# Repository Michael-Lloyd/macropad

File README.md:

# Bluetooth Macropad

Wireless macropad/keypad with programmable keys that lasts a long time between charges. Has some interesting features.

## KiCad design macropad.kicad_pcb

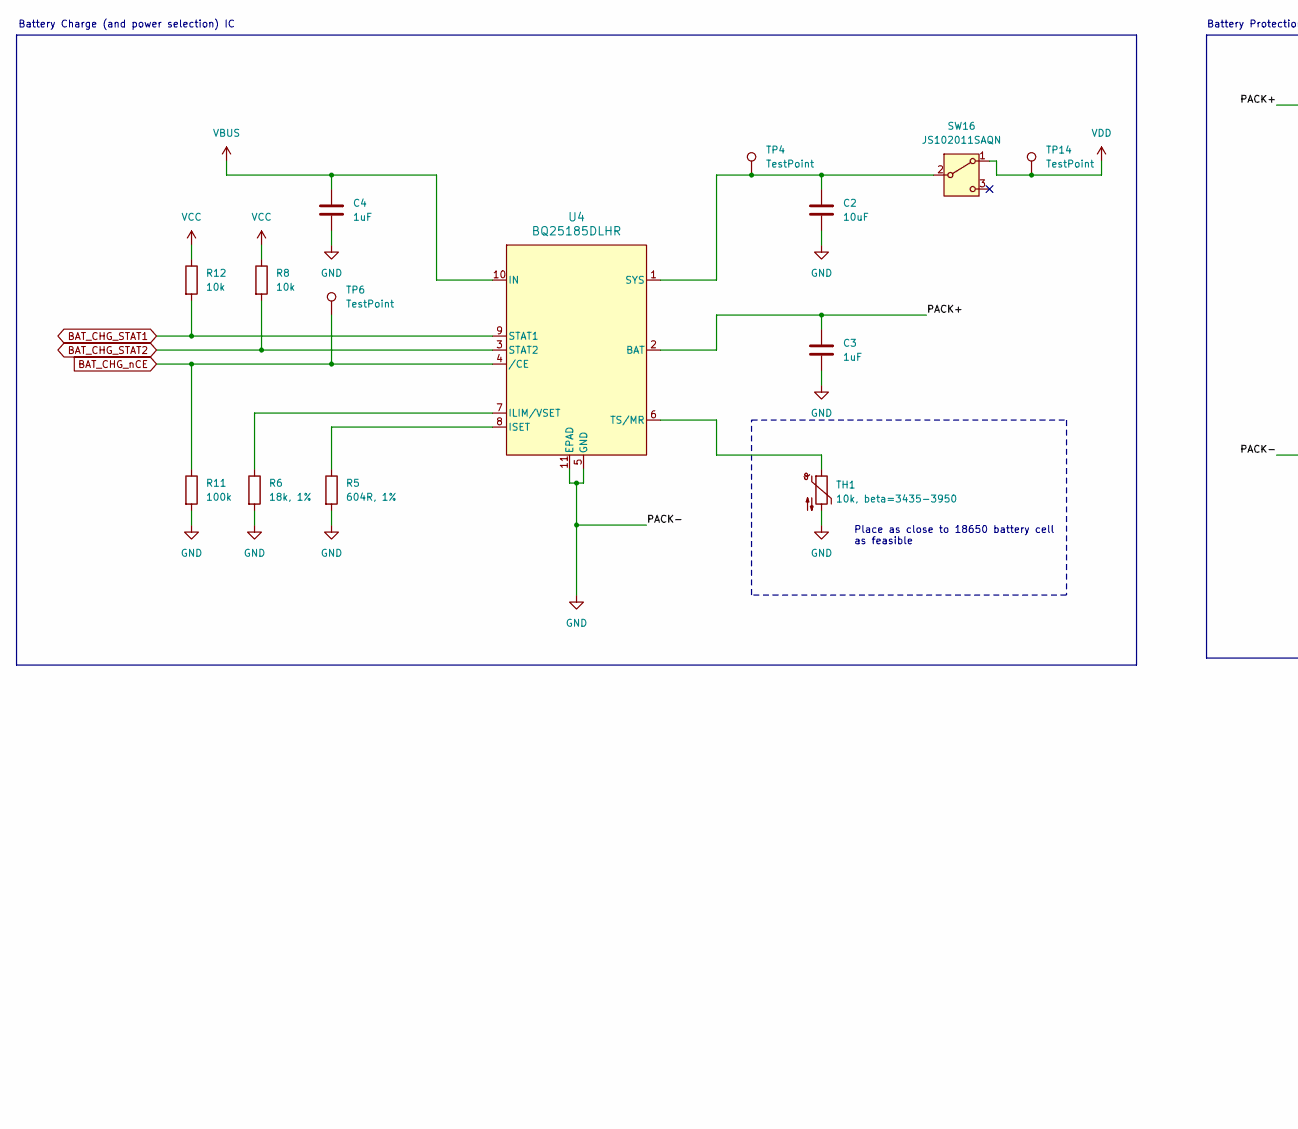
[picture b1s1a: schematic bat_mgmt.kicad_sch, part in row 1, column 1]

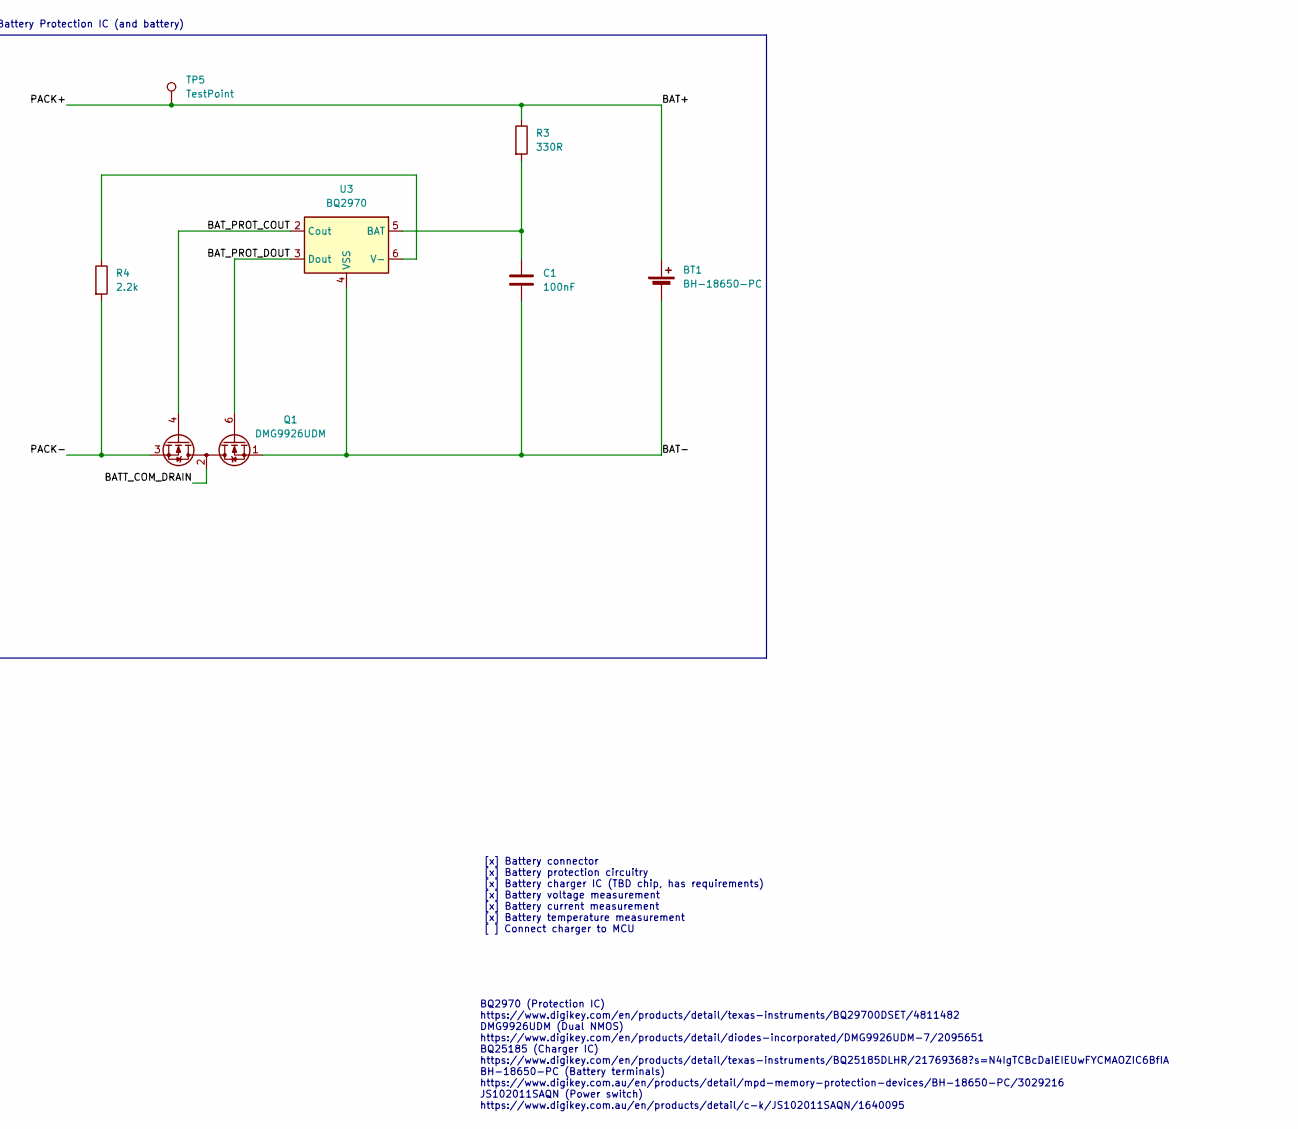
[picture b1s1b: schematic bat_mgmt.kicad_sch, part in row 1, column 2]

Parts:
BT1: BH-18650-PC; BH18650PC
C1: 100nF; C_0402_1005Metric
C2: 10uF; C_0603_1608Metric
C3, C4: 1uF; C_0603_1608Metric
Q1: DMG9926UDM; SOT-23-6
R3: 330R; R_0402_1005Metric
R4: 2.2k; R_0402_1005Metric
R5: 604R, 1%; R_0402_1005Metric
R6: 18k, 1%; R_0402_1005Metric
R8, R12: 10k; R_0402_1005Metric
R11: 100k; R_0402_1005Metric
SW16: JS102011SAQN; SW_SPDT_CK_JS102011SAQN
TH1: 10k, beta=3435-3950; R_0603_1608Metric
TP4, TP5, TP6, TP14: TestPoint; TestPoint_Pad_D0.5mm
U3: BQ2970; WSON-6_1.5x1.5mm_P0.5mm
U4: BQ25185DLHR

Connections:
/Power and Battery Management/BAT+: BT1.1 (+), C3.1, R3.1, TP5.1, U4.2 (BAT)
/Power and Battery Management/BAT-: BT1.2 (-), C1.2, Q1.1 (S1), U3.4 (VSS)
/Power and Battery Management/BATT_COM_DRAIN: Q1.2 (D1/D2), Q1.5 (D1/D2)
/Power and Battery Management/BAT_PROT_COUT: Q1.4 (G2), U3.2 (Cout)
/Power and Battery Management/BAT_PROT_DOUT: Q1.6 (G1), U3.3 (Dout)
BAT_CHG_STAT1: R12.2, U4.9 (STAT1); also elsewhere on the board
BAT_CHG_STAT2: R8.2, U4.3 (STAT2); also elsewhere on the board
BAT_CHG_nCE: R11.1, TP6.1, U4.4 (/CE); also elsewhere on the board
GND: C2.2, C3.2, C4.2, Q1.3 (S2), R4.2, R5.2, R6.2, R11.2, TH1.2, U4.5 (GND), U4.11 (EPAD); also elsewhere on the board
unnamed: C2.1, SW16.2 (B), TP4.1, U4.1 (SYS)
unnamed: C1.1, R3.2, U3.5 (BAT)
unnamed: R4.1, U3.6 (V-)
unnamed: R6.1, U4.7 (ILIM/VSET)
unnamed: R5.1, U4.8 (ISET)
unnamed: TH1.1, U4.6 (TS/MR)
VBUS: C4.1, U4.10 (IN); also elsewhere on the board
VCC: R8.1, R12.1; also elsewhere on the board
VDD: SW16.1 (A), TP14.1; also elsewhere on the board

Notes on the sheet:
[x] Battery connector [x] Battery protection circuitry [x] Battery charger IC (TBD chip, has requirements) [x] Battery voltage measurement [x] Battery current measurement [x] Battery temperature measurement [ ] Connect charger to MCU
Battery Charge (and power selection) IC
BQ2970 (Protection IC) https://www.digikey.com/en/products/detail/texas-instruments/BQ29700DSET/4811482 DMG9926UDM (Dual NMOS) https://www.digikey.com/en/products/detail/diodes-incorporated/DMG9926UDM-7/2095651 BQ25185 (Charger IC) https://www.digikey.com/en/products/detail/texas-instruments/BQ2518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
Place as close to 18650 battery cell as feasible
Battery Protection IC (and battery)

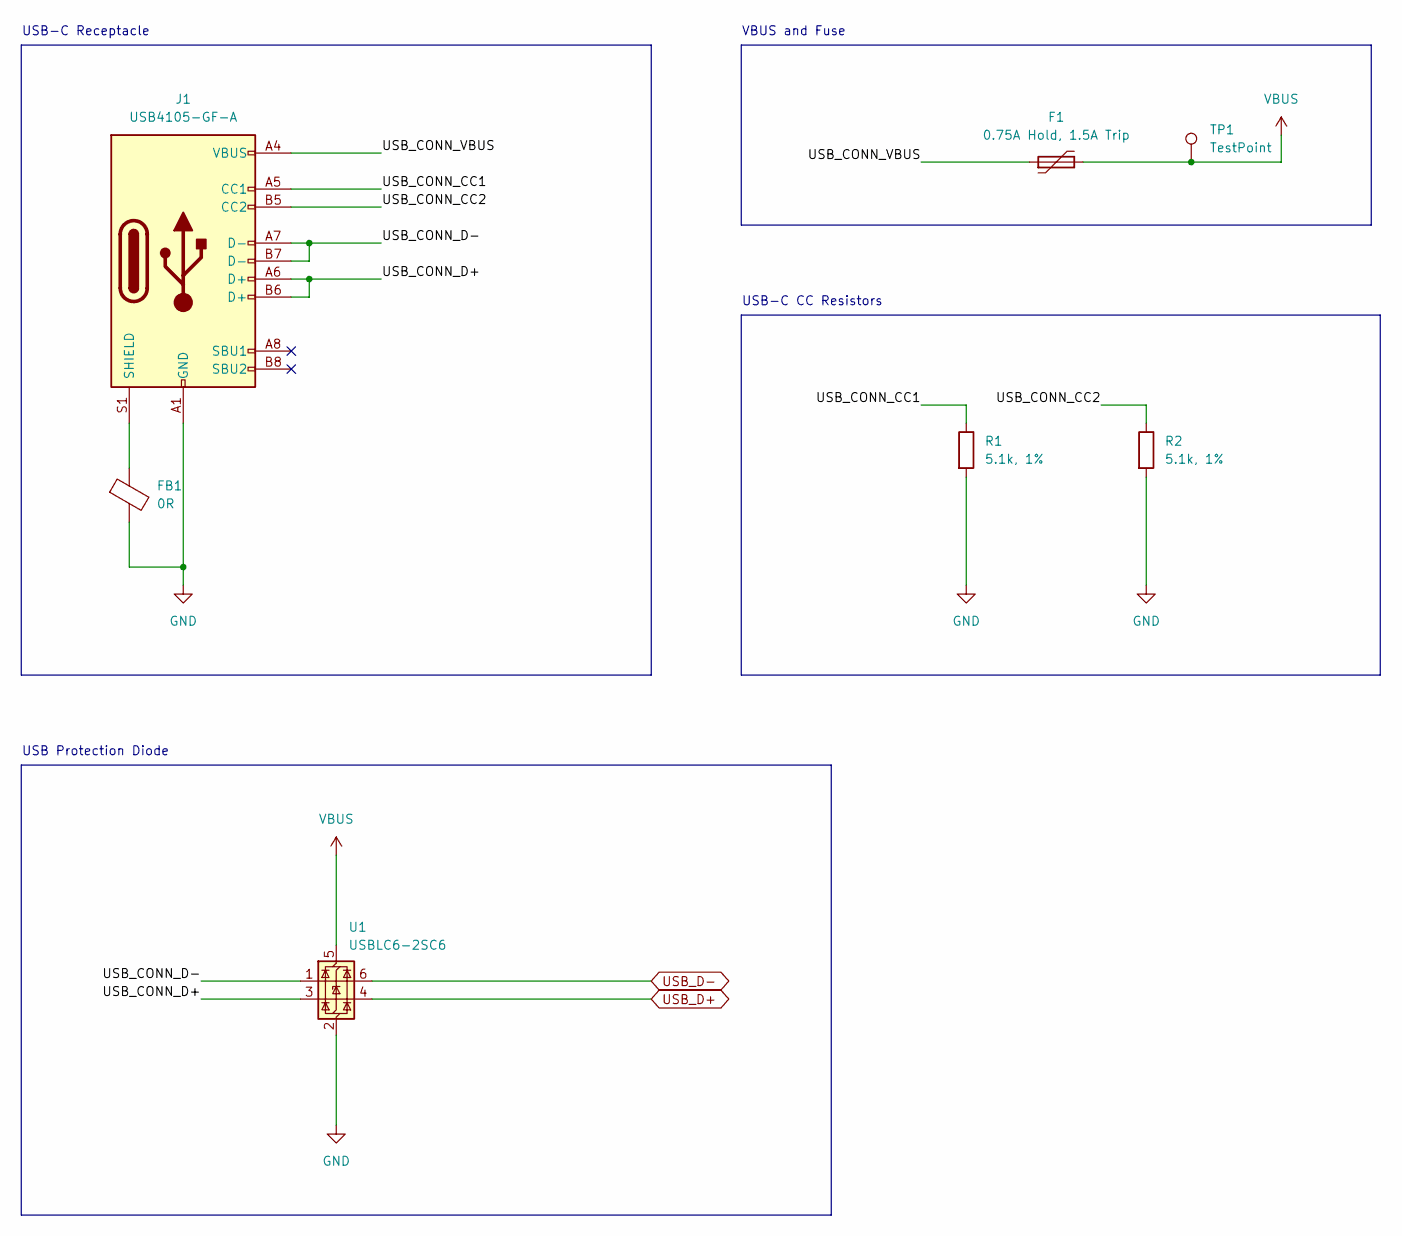
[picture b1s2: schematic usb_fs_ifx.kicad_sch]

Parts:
F1: 0.75A Hold, 1.5A Trip; R_0603_1608Metric
FB1: 0R; R_0402_1005Metric
J1: USB4105-GF-A; USB_C_Receptacle_GCT_USB4105-xx-A_16P_TopMnt_Horizontal
R1, R2: 5.1k, 1%; R_0402_1005Metric
TP1: TestPoint; TestPoint_Pad_D0.5mm
U1: USBLC6-2SC6; SOT-23-6

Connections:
/USB Interface/USB_CONN_CC1: J1.A5 (CC1), R1.1
/USB Interface/USB_CONN_CC2: J1.B5 (CC2), R2.1
/USB Interface/USB_CONN_D+: J1.A6 (D+), J1.B6 (D+), U1.3 (I/O2)
/USB Interface/USB_CONN_D-: J1.A7 (D-), J1.B7 (D-), U1.1 (I/O1)
/USB Interface/USB_CONN_VBUS: F1.1, J1.A4 (VBUS), J1.A9 (VBUS), J1.B4 (VBUS), J1.B9 (VBUS)
GND: FB1.2, J1.A1 (GND), J1.A12 (GND), J1.B1 (GND), J1.B12 (GND), R1.2, R2.2, U1.2 (GND); also elsewhere on the board
unnamed: FB1.1, J1.S1 (SHIELD)
USB_D+: U1.4 (I/O2); also elsewhere on the board
USB_D-: U1.6 (I/O1); also elsewhere on the board
VBUS: F1.2, TP1.1, U1.5 (VBUS); also elsewhere on the board

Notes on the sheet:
USB-C CC Resistors
VBUS and Fuse
USB Protection Diode
USB-C Receptacle

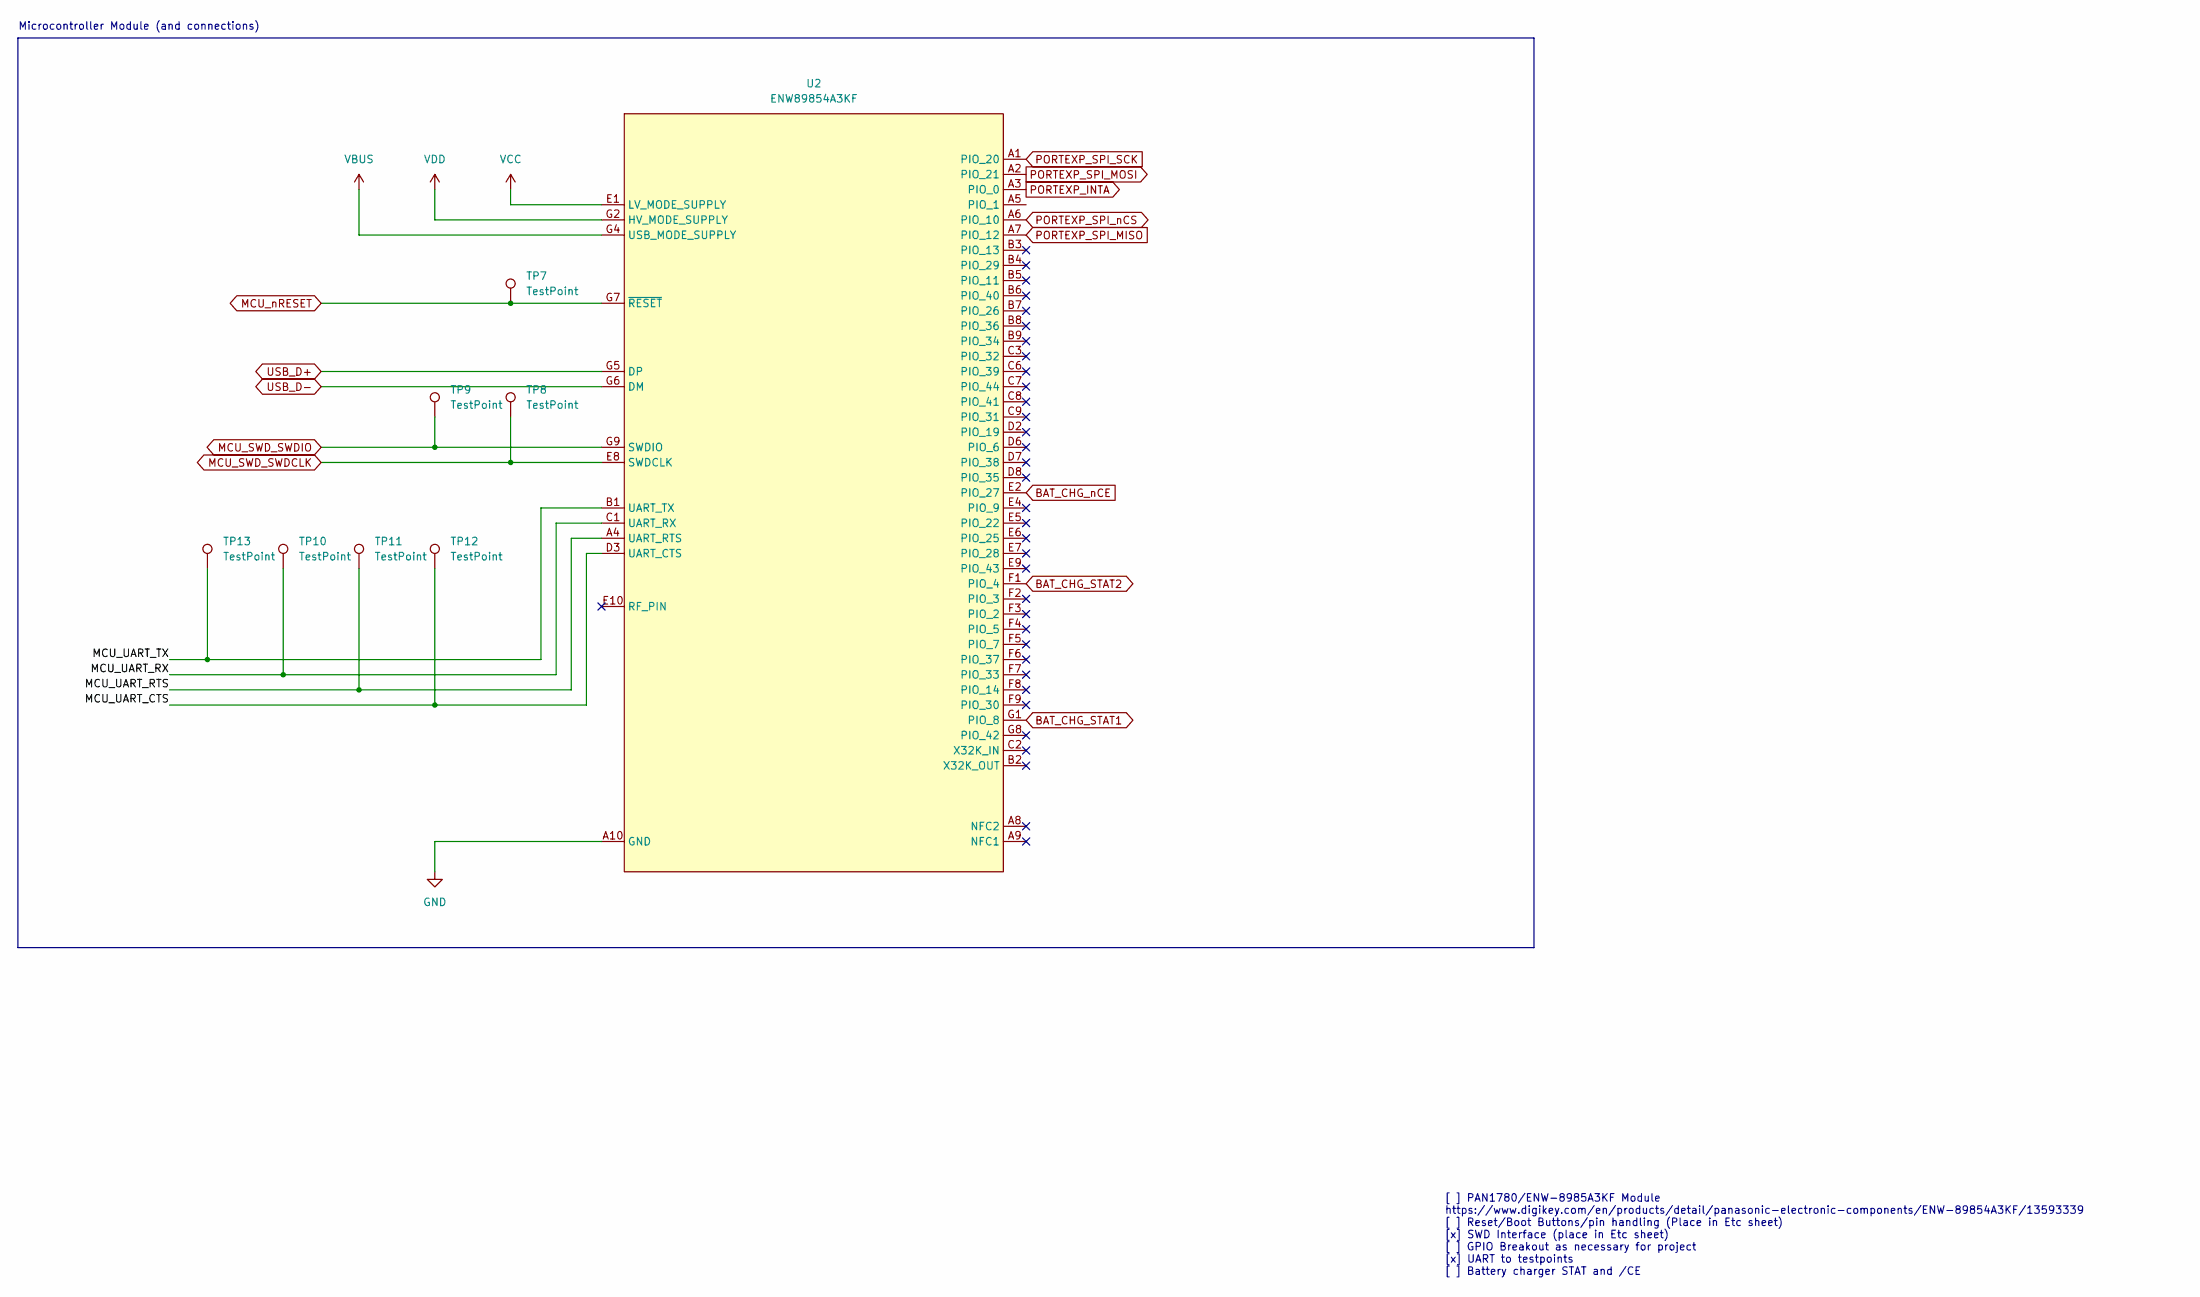
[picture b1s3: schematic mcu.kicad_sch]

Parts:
TP7, TP8, TP9, TP10, TP11, TP12, TP13: TestPoint; TestPoint_Pad_D0.5mm
U2: ENW89854A3KF

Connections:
/Controller/MCU_UART_CTS: TP12.1, U2.D3 (UART_CTS)
/Controller/MCU_UART_RTS: TP11.1, U2.A4 (UART_RTS)
/Controller/MCU_UART_RX: TP10.1, U2.C1 (UART_RX)
/Controller/MCU_UART_TX: TP13.1, U2.B1 (UART_TX)
BAT_CHG_STAT1: U2.G1 (PIO_8); also elsewhere on the board
BAT_CHG_STAT2: U2.F1 (PIO_4); also elsewhere on the board
BAT_CHG_nCE: U2.E2 (PIO_27); also elsewhere on the board
GND: U2.A10 (GND), U2.A12 (GND), U2.A13 (GND), U2.B10 (GND), U2.C4 (GND), U2.C5 (GND), U2.C10 (GND), U2.D1 (GND), U2.D4 (GND), U2.D5 (GND), U2.D9 (GND), U2.D10 (GND), U2.E3 (GND), U2.F10 (GND), U2.G3 (GND), U2.G10 (GND), U2.G12 (GND), U2.G13 (GND); also elsewhere on the board
MCU_SWD_SWDCLK: TP8.1, U2.E8 (SWDCLK); also elsewhere on the board
MCU_SWD_SWDIO: TP9.1, U2.G9 (SWDIO); also elsewhere on the board
MCU_nRESET: TP7.1, U2.G7 (~RESET); also elsewhere on the board
PORTEXP_INTA: U2.A3 (PIO_0); also elsewhere on the board
PORTEXP_SPI_MISO: U2.A7 (PIO_12); also elsewhere on the board
PORTEXP_SPI_MOSI: U2.A2 (PIO_21); also elsewhere on the board
PORTEXP_SPI_SCK: U2.A1 (PIO_20); also elsewhere on the board
PORTEXP_SPI_nCS: U2.A6 (PIO_10); also elsewhere on the board
USB_D+: U2.G5 (DP); also elsewhere on the board
USB_D-: U2.G6 (DM); also elsewhere on the board
VBUS: U2.G4 (USB_MODE_SUPPLY); also elsewhere on the board
VCC: U2.E1 (LV_MODE_SUPPLY); also elsewhere on the board
VDD: U2.G2 (HV_MODE_SUPPLY); also elsewhere on the board

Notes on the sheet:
Microcontroller Module (and connections)
[ ] PAN1780/ENW-8985A3KF Module https://www.digikey.com/en/products/detail/panasonic-electronic-components/ENW-89854A3KF/13593339 [ ] Reset/Boot Buttons/pin handling (Place in Etc sheet) [x] SWD Interface (place in Etc sheet) [ ] GPIO Breakout as necessary for project [x] UART to testpoints [ ] Bat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

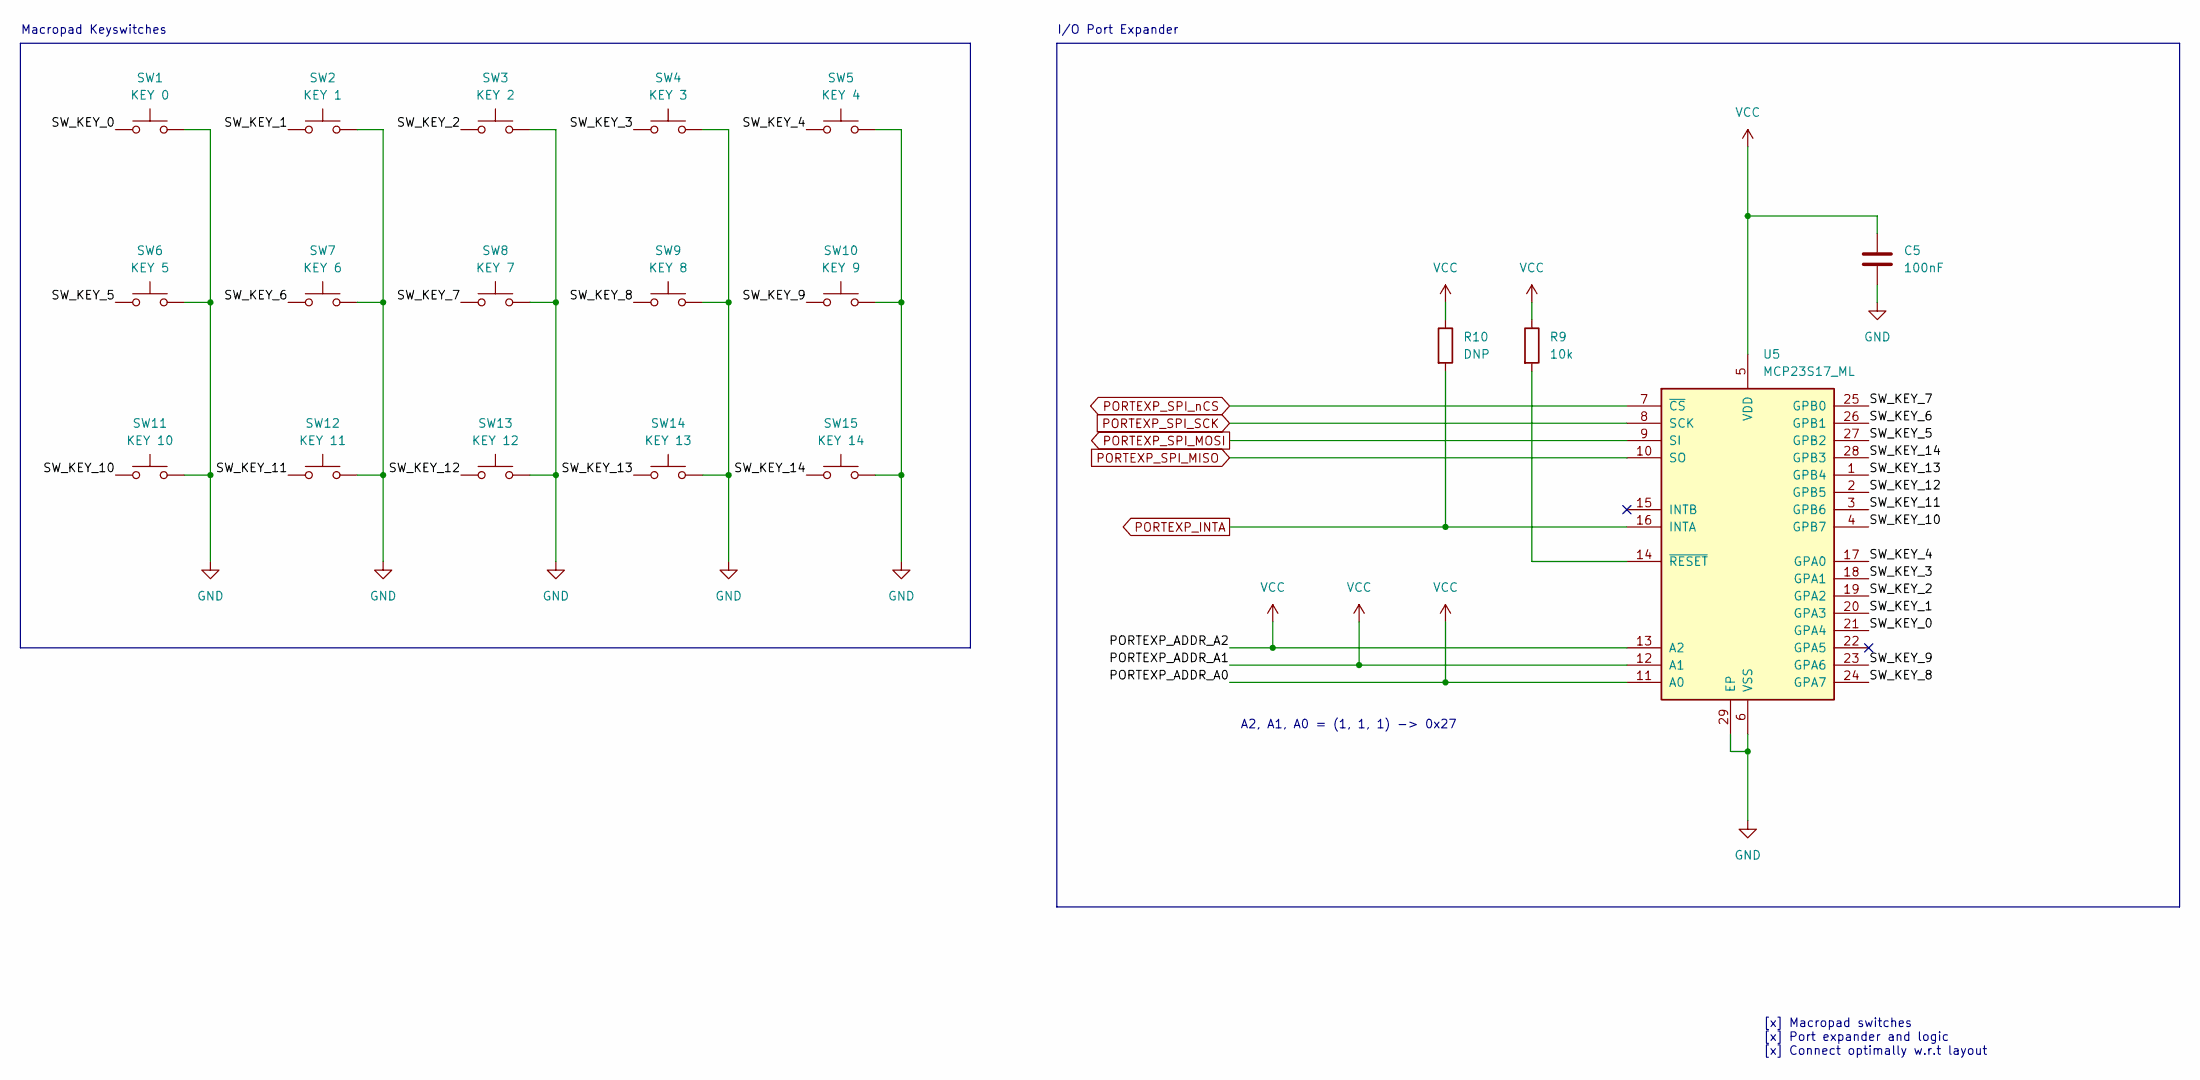
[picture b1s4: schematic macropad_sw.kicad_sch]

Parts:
C5: 100nF; C_0402_1005Metric
R9: 10k; R_0402_1005Metric
R10: DNP; R_0402_1005Metric
SW1: KEY 0; SW_Kailh_Choc_V2_1.00u
SW2: KEY 1; SW_Kailh_Choc_V2_1.00u
SW3: KEY 2; SW_Kailh_Choc_V2_1.00u
SW4: KEY 3; SW_Kailh_Choc_V2_1.00u
SW5: KEY 4; SW_Kailh_Choc_V2_1.00u
SW6: KEY 5; SW_Kailh_Choc_V2_1.00u
SW7: KEY 6; SW_Kailh_Choc_V2_1.00u
SW8: KEY 7; SW_Kailh_Choc_V2_1.00u
SW9: KEY 8; SW_Kailh_Choc_V2_1.00u
SW10: KEY 9; SW_Kailh_Choc_V2_1.00u
SW11: KEY 10; SW_Kailh_Choc_V2_1.00u
SW12: KEY 11; SW_Kailh_Choc_V2_1.00u
SW13: KEY 12; SW_Kailh_Choc_V2_1.00u
SW14: KEY 13; SW_Kailh_Choc_V2_1.00u
SW15: KEY 14; SW_Kailh_Choc_V2_1.00u
U5: MCP23S17_ML; QFN-28-1EP_6x6mm_P0.65mm_EP4.25x4.25mm

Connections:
/Macropad keys/SW_KEY_0: SW1.1, U5.21 (GPA4)
/Macropad keys/SW_KEY_1: SW2.1, U5.20 (GPA3)
/Macropad keys/SW_KEY_2: SW3.1, U5.19 (GPA2)
/Macropad keys/SW_KEY_3: SW4.1, U5.18 (GPA1)
/Macropad keys/SW_KEY_4: SW5.1, U5.17 (GPA0)
/Macropad keys/SW_KEY_5: SW6.1, U5.27 (GPB2)
/Macropad keys/SW_KEY_6: SW7.1, U5.26 (GPB1)
/Macropad keys/SW_KEY_7: SW8.1, U5.25 (GPB0)
/Macropad keys/SW_KEY_8: SW9.1, U5.24 (GPA7)
/Macropad keys/SW_KEY_9: SW10.1, U5.23 (GPA6)
/Macropad keys/SW_KEY_10: SW11.1, U5.4 (GPB7)
/Macropad keys/SW_KEY_11: SW12.1, U5.3 (GPB6)
/Macropad keys/SW_KEY_12: SW13.1, U5.2 (GPB5)
/Macropad keys/SW_KEY_13: SW14.1, U5.1 (GPB4)
/Macropad keys/SW_KEY_14: SW15.1, U5.28 (GPB3)
GND: C5.2, SW1.2, SW2.2, SW3.2, SW4.2, SW5.2, SW6.2, SW7.2, SW8.2, SW9.2, SW10.2, SW11.2, SW12.2, SW13.2, SW14.2, SW15.2, U5.6 (VSS), U5.29 (EP); also elsewhere on the board
unnamed: R9.2, U5.14 (~RESET)
PORTEXP_INTA: R10.2, U5.16 (INTA); also elsewhere on the board
PORTEXP_SPI_MISO: U5.10 (SO); also elsewhere on the board
PORTEXP_SPI_MOSI: U5.9 (SI); also elsewhere on the board
PORTEXP_SPI_SCK: U5.8 (SCK); also elsewhere on the board
PORTEXP_SPI_nCS: U5.7 (~CS); also elsewhere on the board
VCC: C5.1, R9.1, R10.1, U5.5 (VDD), U5.11 (A0), U5.12 (A1), U5.13 (A2); also elsewhere on the board

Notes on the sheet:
Macropad Keyswitches
I/O Port Expander
A2, A1, A0 = (1, 1, 1) -> 0x27
[x] Macropad switches [x] Port expander and logic [x] Connect optimally w.r.t layout

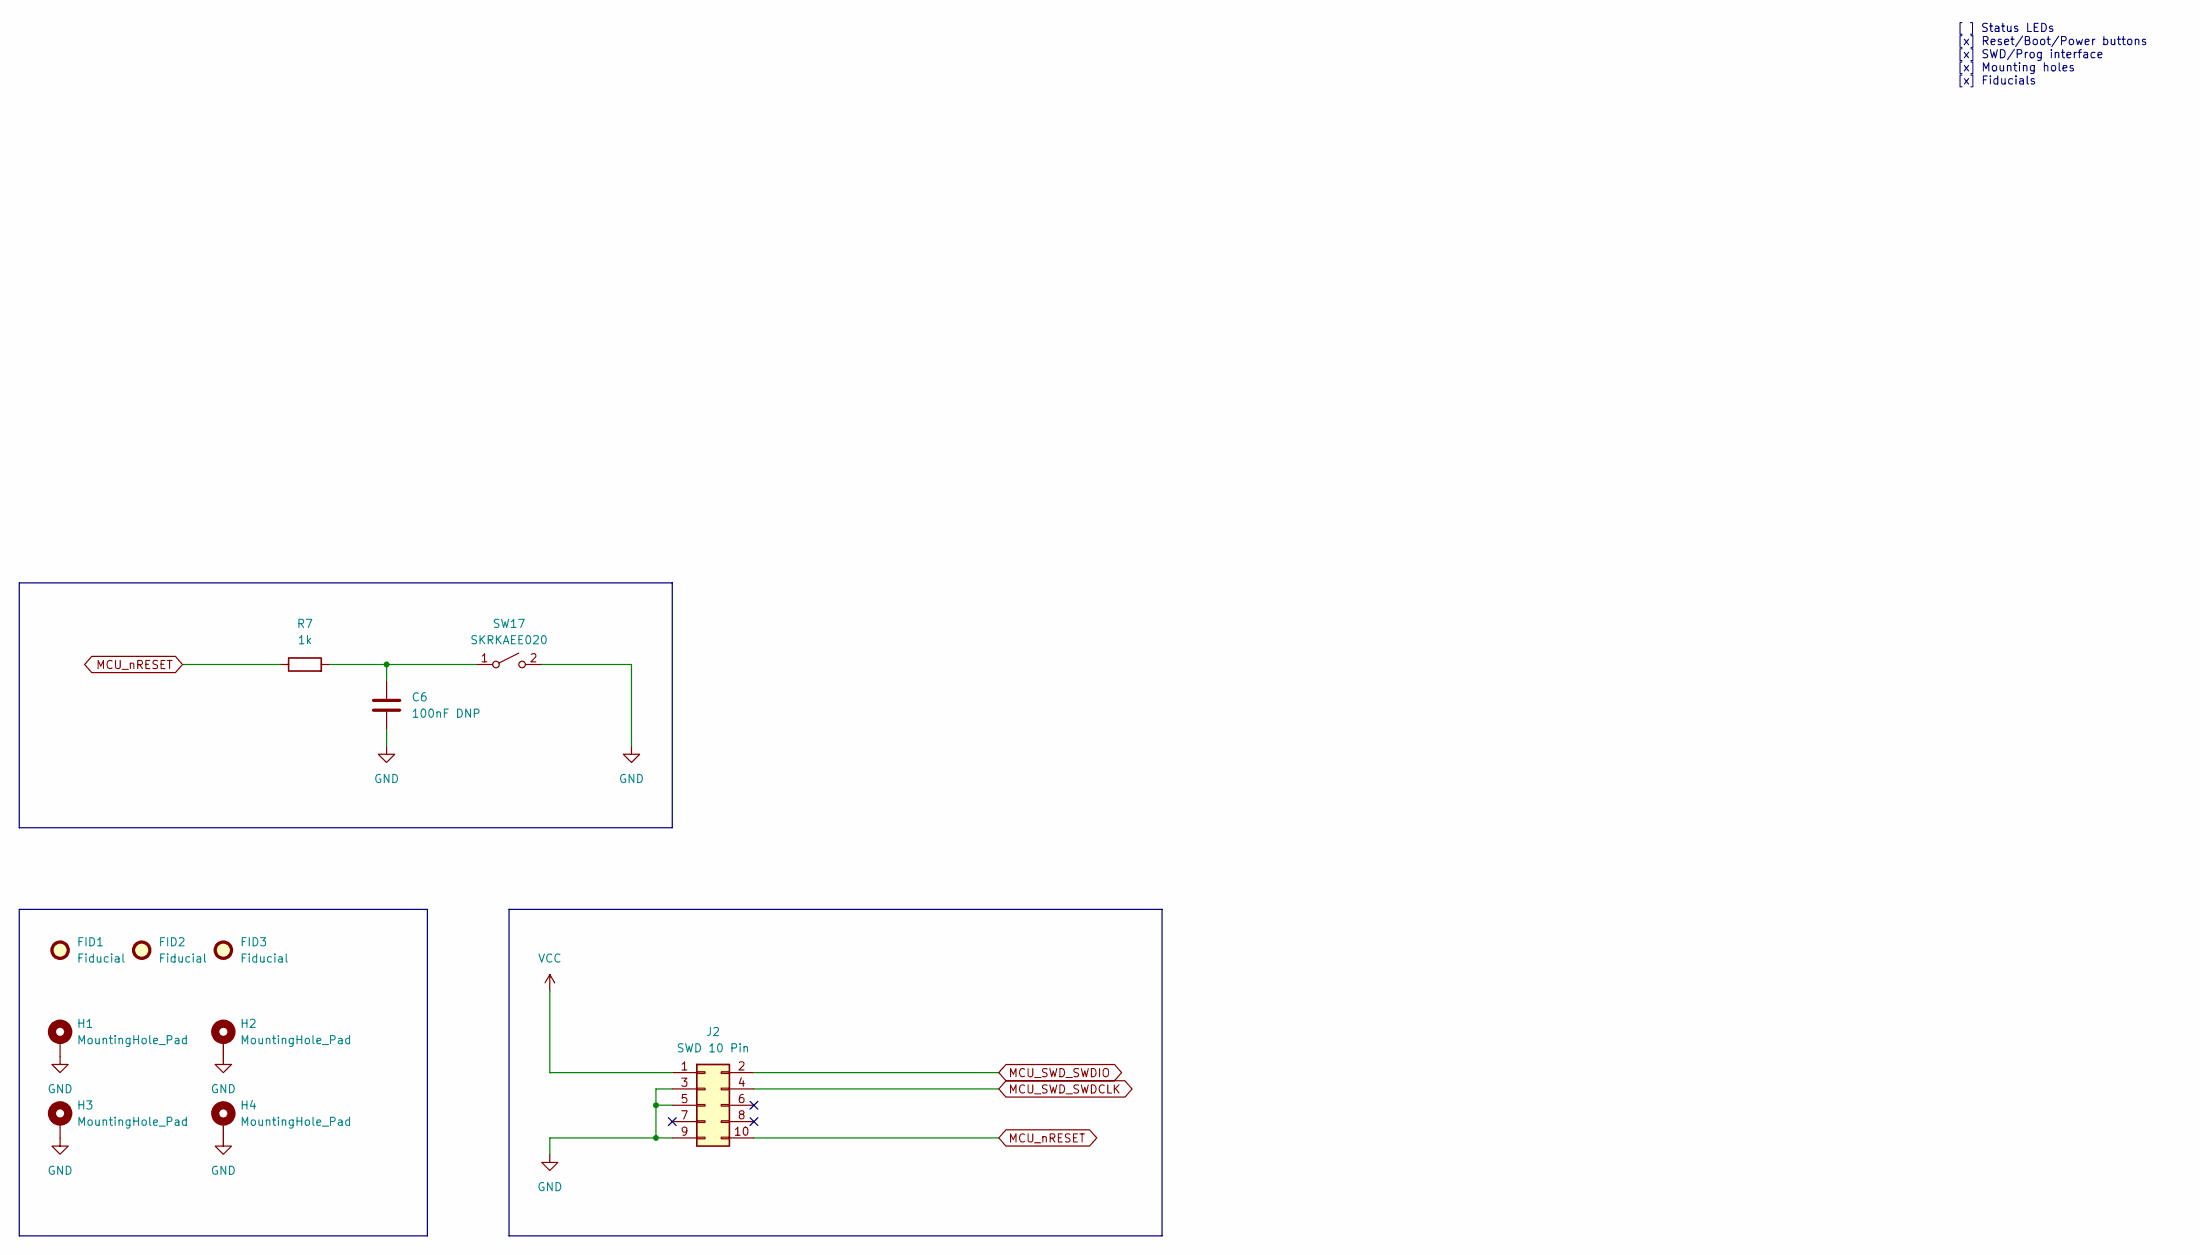
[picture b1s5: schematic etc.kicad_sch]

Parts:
C6: 100nF DNP; C_0402_1005Metric
FID1, FID2, FID3: Fiducial; Fiducial_1mm_Mask2mm
H1, H2, H3, H4: MountingHole_Pad; MountingHole_3.2mm_M3_Pad
J2: SWD 10 Pin; PinHeader_2x05_P1.27mm_Vertical_SMD
R7: 1k; R_0402_1005Metric
SW17: SKRKAEE020; SW_Push_SPST_NO_Alps_SKRK

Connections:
GND: C6.2, H1.1, H2.1, H3.1, H4.1, J2.3, J2.5, J2.9, SW17.2 (B); also elsewhere on the board
MCU_SWD_SWDCLK: J2.4; also elsewhere on the board
MCU_SWD_SWDIO: J2.2; also elsewhere on the board
MCU_nRESET: J2.10, R7.1; also elsewhere on the board
unnamed: C6.1, R7.2, SW17.1 (A)
VCC: J2.1; also elsewhere on the board

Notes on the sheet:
[ ] Status LEDs [x] Reset/Boot/Power buttons [x] SWD/Prog interface [x] Mounting holes [x] Fiducials

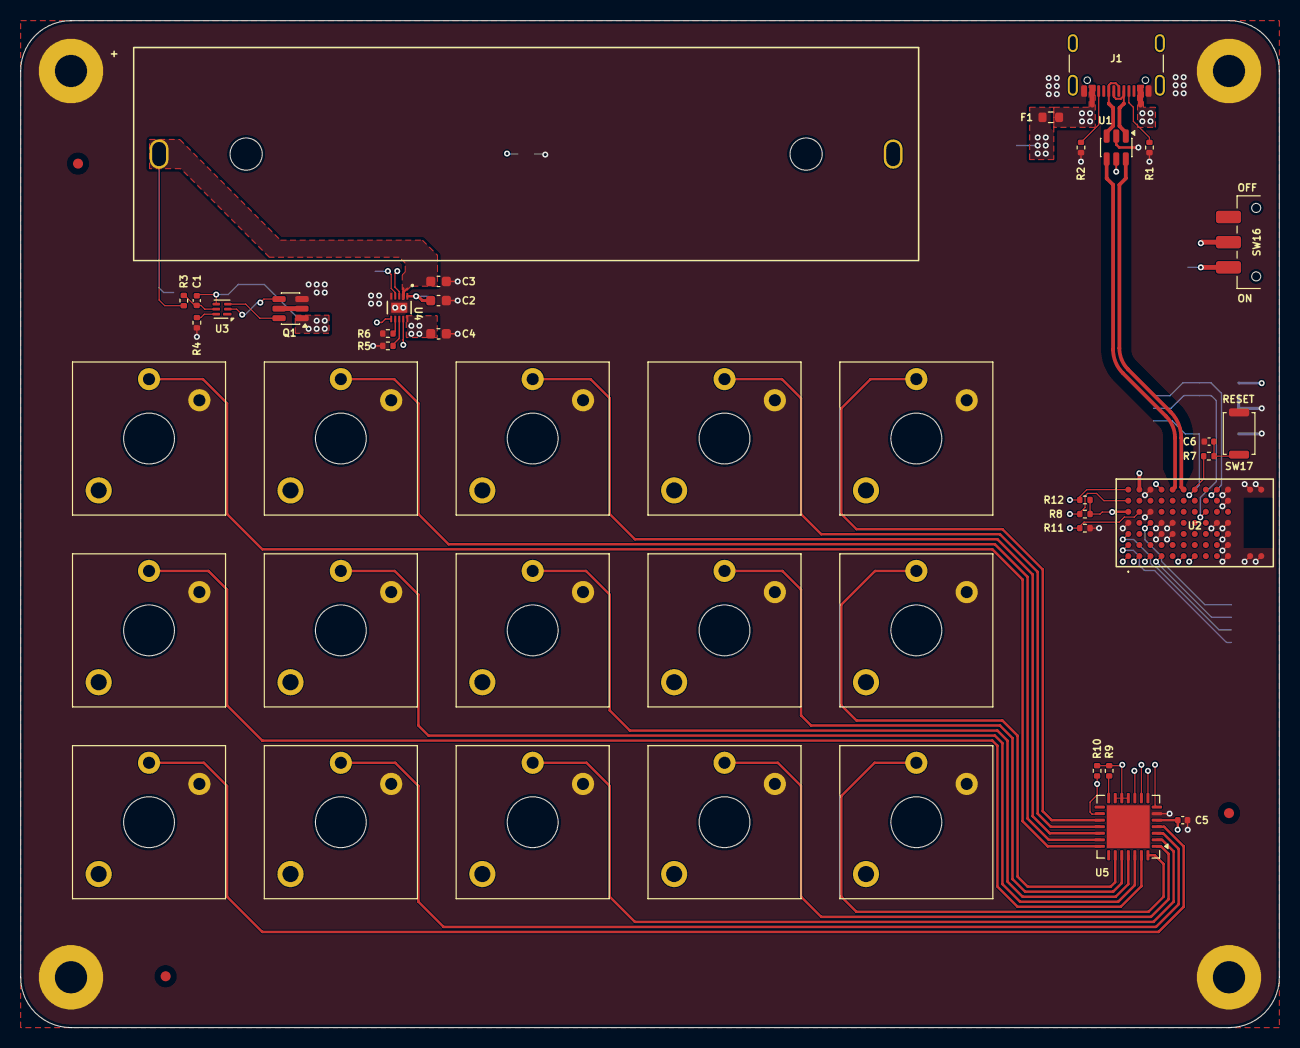
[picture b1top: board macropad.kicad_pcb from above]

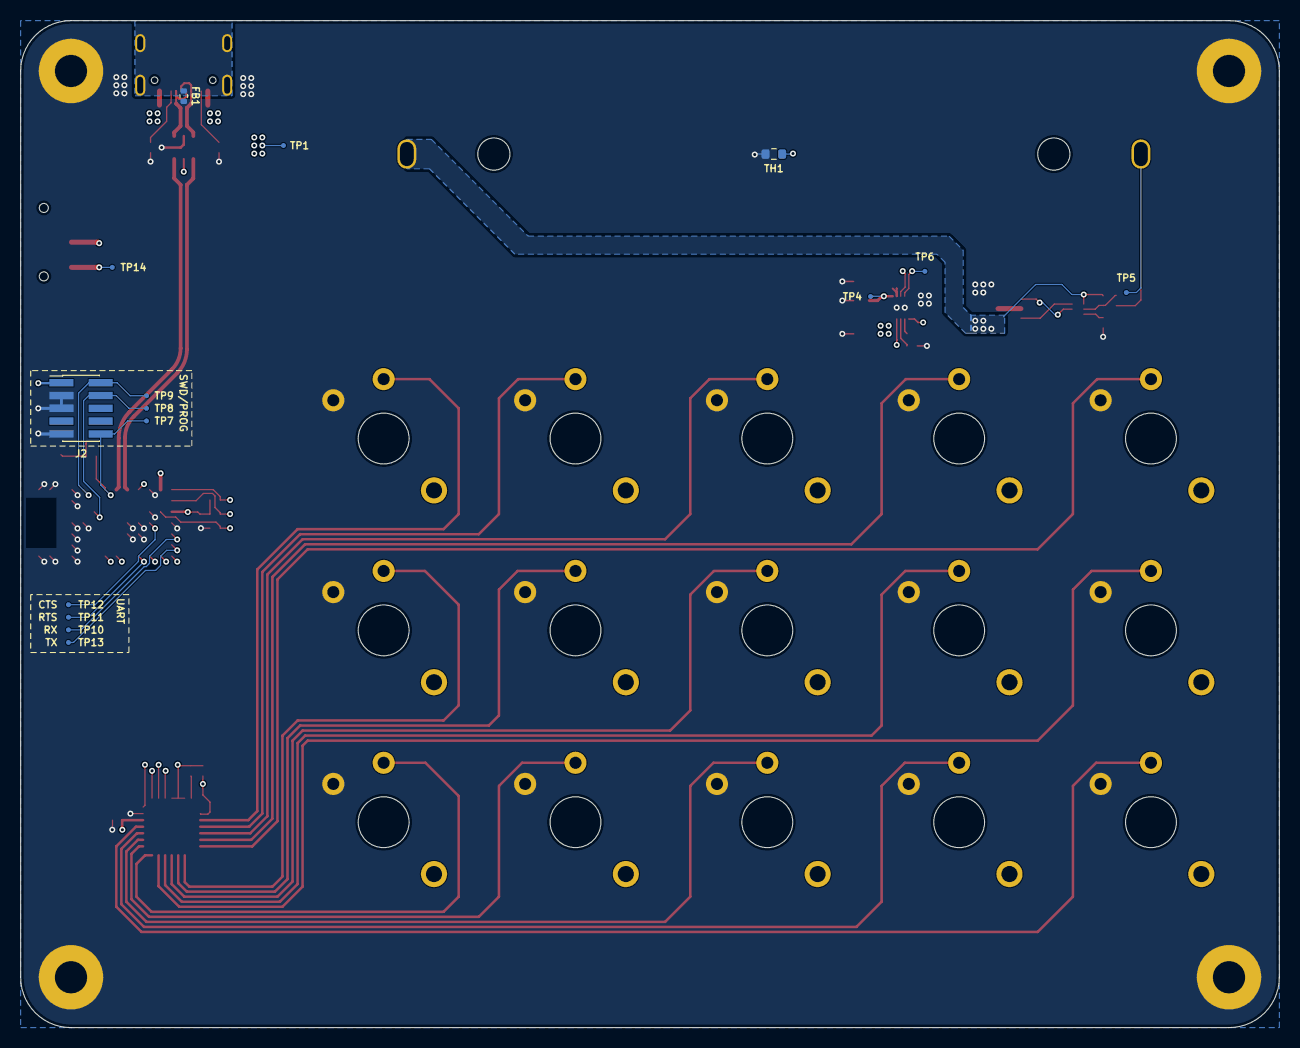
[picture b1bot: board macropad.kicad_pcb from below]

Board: 4 copper layers, 125.0 x 100.0 mm, 66 parts (15 on the bottom side), 55 nets.

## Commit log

2026-01-29 Adding the rest of the lib files
2026-01-29 README added
